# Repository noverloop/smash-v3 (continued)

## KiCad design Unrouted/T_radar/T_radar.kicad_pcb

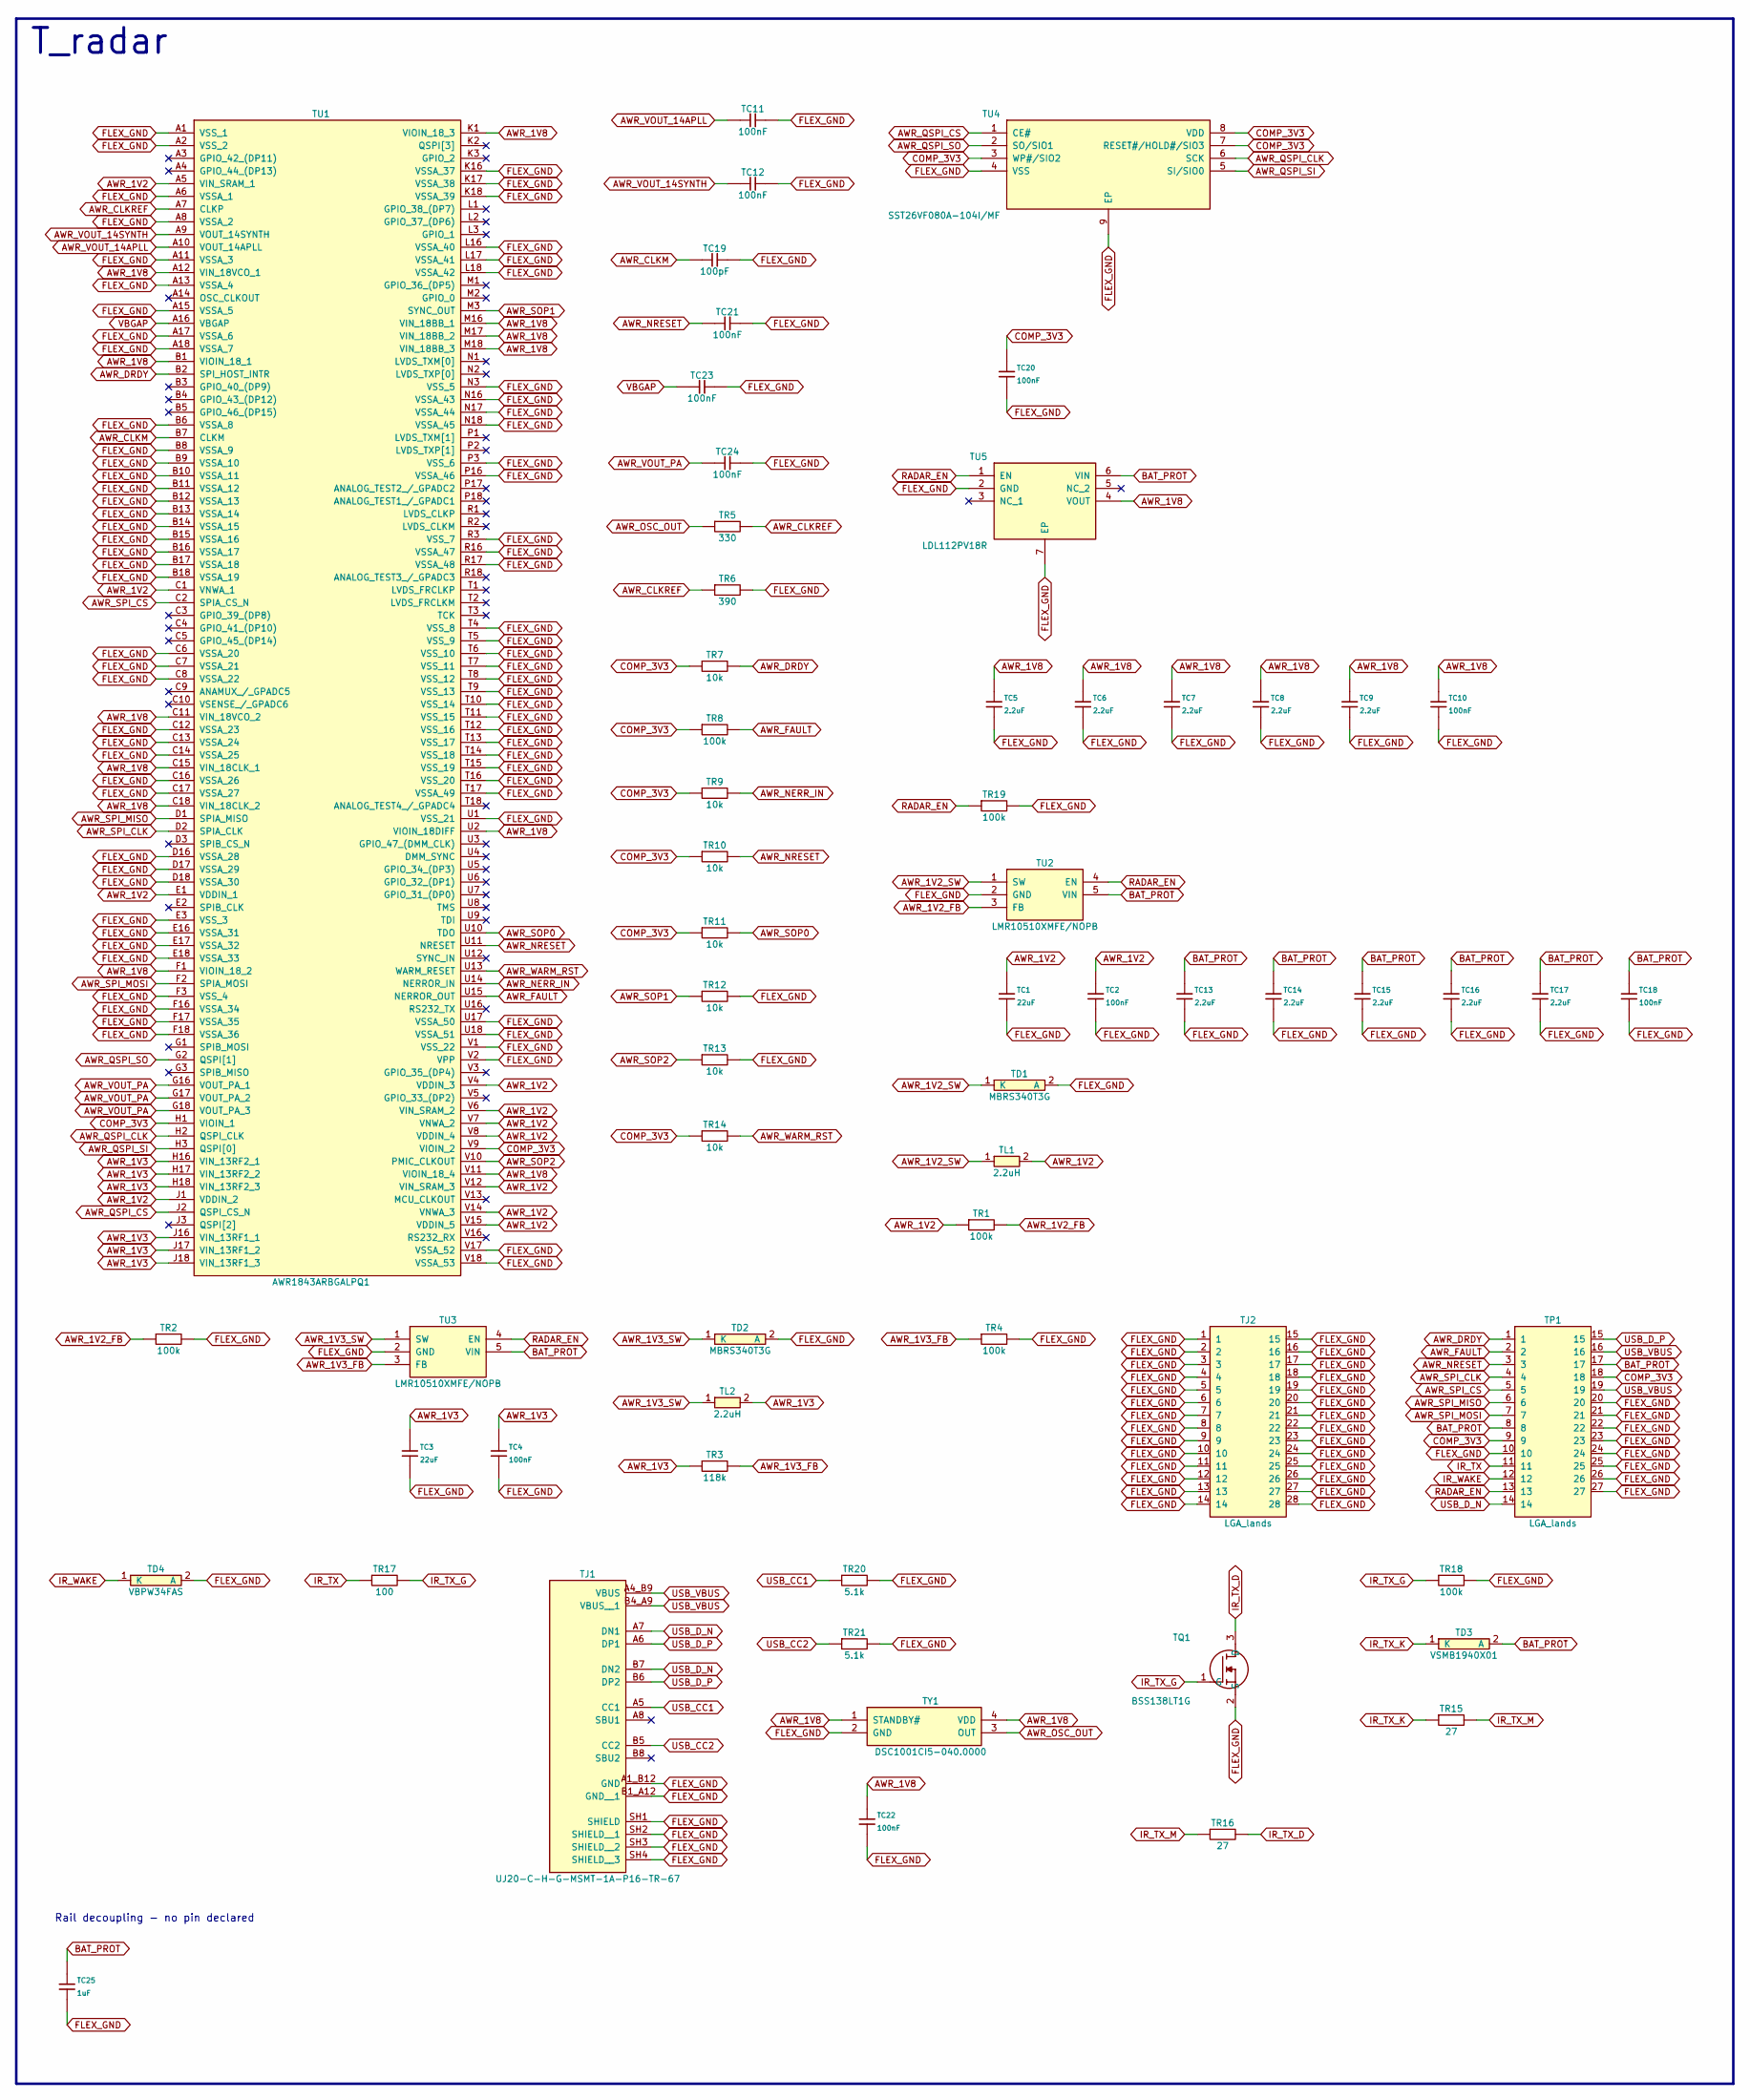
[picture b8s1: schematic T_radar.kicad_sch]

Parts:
TC1, TC3: 22uF; Capacitor_Tantalum_SMD_CP_EIA-3528-12_Kemet-T; MPN T491T 22uF (3528-12 thinnest variant)
TC2, TC4, TC10, TC11, TC12, TC18, TC20, TC21, TC22, TC23, TC24: 100nF; Capacitor_SMD_C_0402_1005Metric; MPN C0402 X7R 100nF
TC5, TC6, TC7, TC8, TC9, TC13, TC14, TC15, TC16, TC17: 2.2uF; Capacitor_SMD_C_0603_1608Metric; MPN C-Series MIL-PRF-32535 X7R 0603 2.2uF
TC19: 100pF; Capacitor_SMD_C_0603_1608Metric; MPN SQCSVA 100pF
TC25: 1uF; Capacitor_SMD_C_0805_2012Metric; MPN C-Series MIL-PRF-32535 X7R 0805 1uF
TD1, TD2: MBRS340T3G; DIOM8059X261N; MPN MBRS340T3G
TD3: VSMB1940X01; MPN VSMB1940X01
TD4: VBPW34FAS; MPN VBPW34FAS
TJ1: UJ20-C-H-G-MSMT-1A-P16-TR-67; SAMESKY_UJ20-C-H-G-MSMT-1A-P16-TR-67; MPN UJ20-C-H-G-MSMT-1A-P16-TR-67
TJ2: LGA_lands; J_radar_module_spacer_radar_module_nose_cap; MPN LGA_lands
TL1, TL2: 2.2uH; Inductor_SMD_L_2012_2.0x1.25mm; MPN TMS201210ALM-2R2MTAA
TP1: LGA_lands; P_radar_module_spacer_companion_compute_radar_module; MPN LGA_lands
TQ1: BSS138LT1G; SOT96P237X111-3N; MPN BSS138LT1G
TR1, TR2, TR4, TR8, TR18, TR19: 100k; Resistor_SMD_R_0402_1005Metric; MPN CRCW0402 100k 1% e3
TR3: 118k; Resistor_SMD_R_0402_1005Metric; MPN CRCW0402 118k 1% e3
TR5: 330; Resistor_SMD_R_0402_1005Metric; MPN CRCW0402 330 1% e3
TR6: 390; Resistor_SMD_R_0402_1005Metric; MPN CRCW0402 390 1% e3
TR7, TR9, TR10, TR11, TR12, TR13, TR14: 10k; Resistor_SMD_R_0402_1005Metric; MPN CRCW0402 10k 1% e3
TR15, TR16: 27; Resistor_SMD_R_0402_1005Metric; MPN CRCW0402 27 1% e3
TR17: 100; Resistor_SMD_R_0402_1005Metric; MPN CRCW0402 100 1% e3
TR20, TR21: 5.1k; Resistor_SMD_R_0402_1005Metric; MPN CRCW0402 5.1k 1% e3
TU1: AWR1843ARBGALPQ1; BGA180C80P18X18_1500X1500X96; MPN AWR1843ARBGALPQ1
TU2, TU3: LMR10510XMFE/NOPB; SOT95P280X145-5N; MPN LMR10510XMFE/NOPB
TU4: SST26VF080A-104I/MF; SON127P600X500X80-9N-D; MPN SST26VF080A-104I/MF
TU5: LDL112PV18R; SON95P300X300X100-7N-D; MPN LDL112PV18R
TY1: DSC1001CI5-040.0000; DSC1001CI50080000; MPN DSC1001CI5-040.0000

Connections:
AWR_1V2: TC1.1, TC2.1, TL1.2, TR1.1, TU1.A5 (VIN_SRAM_1), TU1.C1 (VNWA_1), TU1.E1 (VDDIN_1), TU1.J1 (VDDIN_2), TU1.V4 (VDDIN_3), TU1.V6 (VIN_SRAM_2), TU1.V7 (VNWA_2), TU1.V8 (VDDIN_4), TU1.V12 (VIN_SRAM_3), TU1.V14 (VNWA_3), TU1.V15 (VDDIN_5)
AWR_1V2_FB: TR1.2, TR2.1, TU2.3 (FB)
AWR_1V2_SW: TD1.1 (K), TL1.1, TU2.1 (SW)
AWR_1V3: TC3.1, TC4.1, TL2.2, TR3.1, TU1.H16 (VIN_13RF2_1), TU1.H17 (VIN_13RF2_2), TU1.H18 (VIN_13RF2_3), TU1.J16 (VIN_13RF1_1), TU1.J17 (VIN_13RF1_2), TU1.J18 (VIN_13RF1_3)
AWR_1V3_FB: TR3.2, TR4.1, TU3.3 (FB)
AWR_1V3_SW: TD2.1 (K), TL2.1, TU3.1 (SW)
AWR_1V8: TC5.1, TC6.1, TC7.1, TC8.1, TC9.1, TC10.1, TC22.1, TU1.A12 (VIN_18VCO_1), TU1.B1 (VIOIN_18_1), TU1.C11 (VIN_18VCO_2), TU1.C15 (VIN_18CLK_1), TU1.C18 (VIN_18CLK_2), TU1.F1 (VIOIN_18_2), TU1.K1 (VIOIN_18_3), TU1.M16 (VIN_18BB_1), TU1.M17 (VIN_18BB_2), TU1.M18 (VIN_18BB_3), TU1.U2 (VIOIN_18DIFF), TU1.V11 (VIOIN_18_4), TU5.4 (VOUT), TY1.1 (STANDBY#), TY1.4 (VDD)
AWR_CLKM: TC19.1, TU1.B7 (CLKM)
AWR_CLKREF: TR5.2, TR6.1, TU1.A7 (CLKP)
AWR_DRDY: TP1.1, TR7.2, TU1.B2 (SPI_HOST_INTR)
AWR_FAULT: TP1.2, TR8.2, TU1.U15 (NERROR_OUT)
AWR_NERR_IN: TR9.2, TU1.U14 (NERROR_IN)
AWR_NRESET: TC21.1, TP1.3, TR10.2, TU1.U11 (NRESET)
AWR_OSC_OUT: TR5.1, TY1.3 (OUT)
AWR_QSPI_CLK: TU1.H2 (QSPI_CLK), TU4.6 (SCK)
AWR_QSPI_CS: TU1.J2 (QSPI_CS_N), TU4.1 (CE#)
AWR_QSPI_SI: TU1.H3 (QSPI[0]), TU4.5 (SI/SIO0)
AWR_QSPI_SO: TU1.G2 (QSPI[1]), TU4.2 (SO/SIO1)
AWR_SOP0: TR11.2, TU1.U10 (TDO)
AWR_SOP1: TR12.1, TU1.M3 (SYNC_OUT)
AWR_SOP2: TR13.1, TU1.V10 (PMIC_CLKOUT)
AWR_SPI_CLK: TP1.4, TU1.D2 (SPIA_CLK)
AWR_SPI_CS: TP1.5, TU1.C2 (SPIA_CS_N)
AWR_SPI_MISO: TP1.6, TU1.D1 (SPIA_MISO)
AWR_SPI_MOSI: TP1.7, TU1.F2 (SPIA_MOSI)
AWR_VOUT_14APLL: TC11.1, TU1.A10 (VOUT_14APLL)
AWR_VOUT_14SYNTH: TC12.1, TU1.A9 (VOUT_14SYNTH)
AWR_VOUT_PA: TC24.1, TU1.G16 (VOUT_PA_1), TU1.G17 (VOUT_PA_2), TU1.G18 (VOUT_PA_3)
AWR_WARM_RST: TR14.2, TU1.U13 (WARM_RESET)
BAT_PROT: TC13.1, TC14.1, TC15.1, TC16.1, TC17.1, TC18.1, TC25.1, TD3.2 (A), TP1.8, TP1.17, TU2.5 (VIN), TU3.5 (VIN), TU5.6 (VIN)
COMP_3V3: TC20.1, TP1.9, TP1.18, TR7.1, TR8.1, TR9.1, TR10.1, TR11.1, TR14.1, TU1.H1 (VIOIN_1), TU1.V9 (VIOIN_2), TU4.3 (WP#/SIO2), TU4.7 (RESET#/HOLD#/SIO3), TU4.8 (VDD)
FLEX_GND: TC1.2, TC2.2, TC3.2, TC4.2, TC5.2, TC6.2, TC7.2, TC8.2, TC9.2, TC10.2, TC11.2, TC12.2, TC13.2, TC14.2, TC15.2, TC16.2, TC17.2, TC18.2, TC19.2, TC20.2, TC21.2, TC22.2, TC23.2, TC24.2, TC25.2, TD1.2 (A), TD2.2 (A), TD4.2 (A), TJ1.A1_B12 (GND), TJ1.B1_A12 (GND__1), TJ1.SH1 (SHIELD), TJ1.SH2 (SHIELD__1), TJ1.SH3 (SHIELD__2), TJ1.SH4 (SHIELD__3), TJ2.1, TJ2.2, TJ2.3, TJ2.4, TJ2.5, TJ2.6, TJ2.7, TJ2.8, TJ2.9, TJ2.10, TJ2.11, TJ2.12, TJ2.13, TJ2.14, TJ2.15, TJ2.16, TJ2.17, TJ2.18, TJ2.19, TJ2.20, TJ2.21, TJ2.22, TJ2.23, TJ2.24, TJ2.25, TJ2.26, TJ2.27, TJ2.28, TP1.10, TP1.20, TP1.21, TP1.22, TP1.23, TP1.24, TP1.25, TP1.26, TP1.27, TQ1.2 (S), TR2.2, TR4.2, TR6.2, TR12.2, TR13.2, TR18.2, TR19.2, TR20.2, TR21.2, TU1.A1 (VSS_1), TU1.A2 (VSS_2), TU1.A6 (VSSA_1), TU1.A8 (VSSA_2), TU1.A11 (VSSA_3), TU1.A13 (VSSA_4), TU1.A15 (VSSA_5), TU1.A17 (VSSA_6), TU1.A18 (VSSA_7), TU1.B6 (VSSA_8), TU1.B8 (VSSA_9), TU1.B9 (VSSA_10), TU1.B10 (VSSA_11), TU1.B11 (VSSA_12), TU1.B12 (VSSA_13), TU1.B13 (VSSA_14), TU1.B14 (VSSA_15), TU1.B15 (VSSA_16), TU1.B16 (VSSA_17), TU1.B17 (VSSA_18), TU1.B18 (VSSA_19), TU1.C6 (VSSA_20), TU1.C7 (VSSA_21), TU1.C8 (VSSA_22), TU1.C12 (VSSA_23), TU1.C13 (VSSA_24), TU1.C14 (VSSA_25), TU1.C16 (VSSA_26), TU1.C17 (VSSA_27), TU1.D16 (VSSA_28), TU1.D17 (VSSA_29), TU1.D18 (VSSA_30), TU1.E3 (VSS_3), TU1.E16 (VSSA_31), TU1.E17 (VSSA_32), TU1.E18 (VSSA_33), TU1.F3 (VSS_4), TU1.F16 (VSSA_34), TU1.F17 (VSSA_35), TU1.F18 (VSSA_36), TU1.K16 (VSSA_37), TU1.K17 (VSSA_38), TU1.K18 (VSSA_39), TU1.L16 (VSSA_40), TU1.L17 (VSSA_41), TU1.L18 (VSSA_42), TU1.N3 (VSS_5), TU1.N16 (VSSA_43), TU1.N17 (VSSA_44), TU1.N18 (VSSA_45), TU1.P3 (VSS_6), TU1.P16 (VSSA_46), TU1.R3 (VSS_7), TU1.R16 (VSSA_47), TU1.R17 (VSSA_48), TU1.T4 (VSS_8), TU1.T5 (VSS_9), TU1.T6 (VSS_10), TU1.T7 (VSS_11), TU1.T8 (VSS_12), TU1.T9 (VSS_13), TU1.T10 (VSS_14), TU1.T11 (VSS_15), TU1.T12 (VSS_16), TU1.T13 (VSS_17), TU1.T14 (VSS_18), TU1.T15 (VSS_19), TU1.T16 (VSS_20), TU1.T17 (VSSA_49), TU1.U1 (VSS_21), TU1.U17 (VSSA_50), TU1.U18 (VSSA_51), TU1.V1 (VSS_22), TU1.V2 (VPP), TU1.V17 (VSSA_52), TU1.V18 (VSSA_53), TU2.2 (GND), TU3.2 (GND), TU4.4 (VSS), TU4.9 (EP), TU5.2 (GND), TU5.7 (EP), TY1.2 (GND)
IR_TX: TP1.11, TR17.1
IR_TX_D: TQ1.3 (D), TR16.2
IR_TX_G: TQ1.1 (G), TR17.2, TR18.1
IR_TX_K: TD3.1 (K), TR15.1
IR_TX_M: TR15.2, TR16.1
IR_WAKE: TD4.1 (K), TP1.12
RADAR_EN: TP1.13, TR19.1, TU2.4 (EN), TU3.4 (EN), TU5.1 (EN)
USB_CC1: TJ1.A5 (CC1), TR20.1
USB_CC2: TJ1.B5 (CC2), TR21.1
USB_D_N: TJ1.A7 (DN1), TJ1.B7 (DN2), TP1.14
USB_D_P: TJ1.A6 (DP1), TJ1.B6 (DP2), TP1.15
USB_VBUS: TJ1.A4_B9 (VBUS), TJ1.B4_A9 (VBUS__1), TP1.16, TP1.19
VBGAP: TC23.1, TU1.A16 (VBGAP)

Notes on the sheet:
T_radar
Rail decoupling - no pin declared

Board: 20 copper layers, 64 parts (54 on the bottom side), 45 nets, no tracks yet.

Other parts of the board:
TMH1, TMH2: smash_mech_potting
